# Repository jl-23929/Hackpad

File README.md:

# Hackpad

A 10-key macropad with a diagnostic LED for debugging. It's based on a Seeed XIAO RP2040.

# PCB

This is my PCB. I made it using KiCAD. It is 60x85mm and uses 2 layers with no vias.

# Enclosure

I designed the enclosure using OnShape (Fusion was completely broken at the time).

The PCB is held in with two M3 standoffs.

The bottom of the case has been countersunk for the bolt-heads.

# BOM
To build the Hackpad, the following parts are required:

11 x Cherry MX Switches
10 x Keycaps
1 x WS2812B LEDs
1 x Seeed XIAO RP2040.
1 x PCB
1 x Case (Four 3D-printed parts)
2 x 20mm M3 bolts
2 x M3 Nyloc Nuts

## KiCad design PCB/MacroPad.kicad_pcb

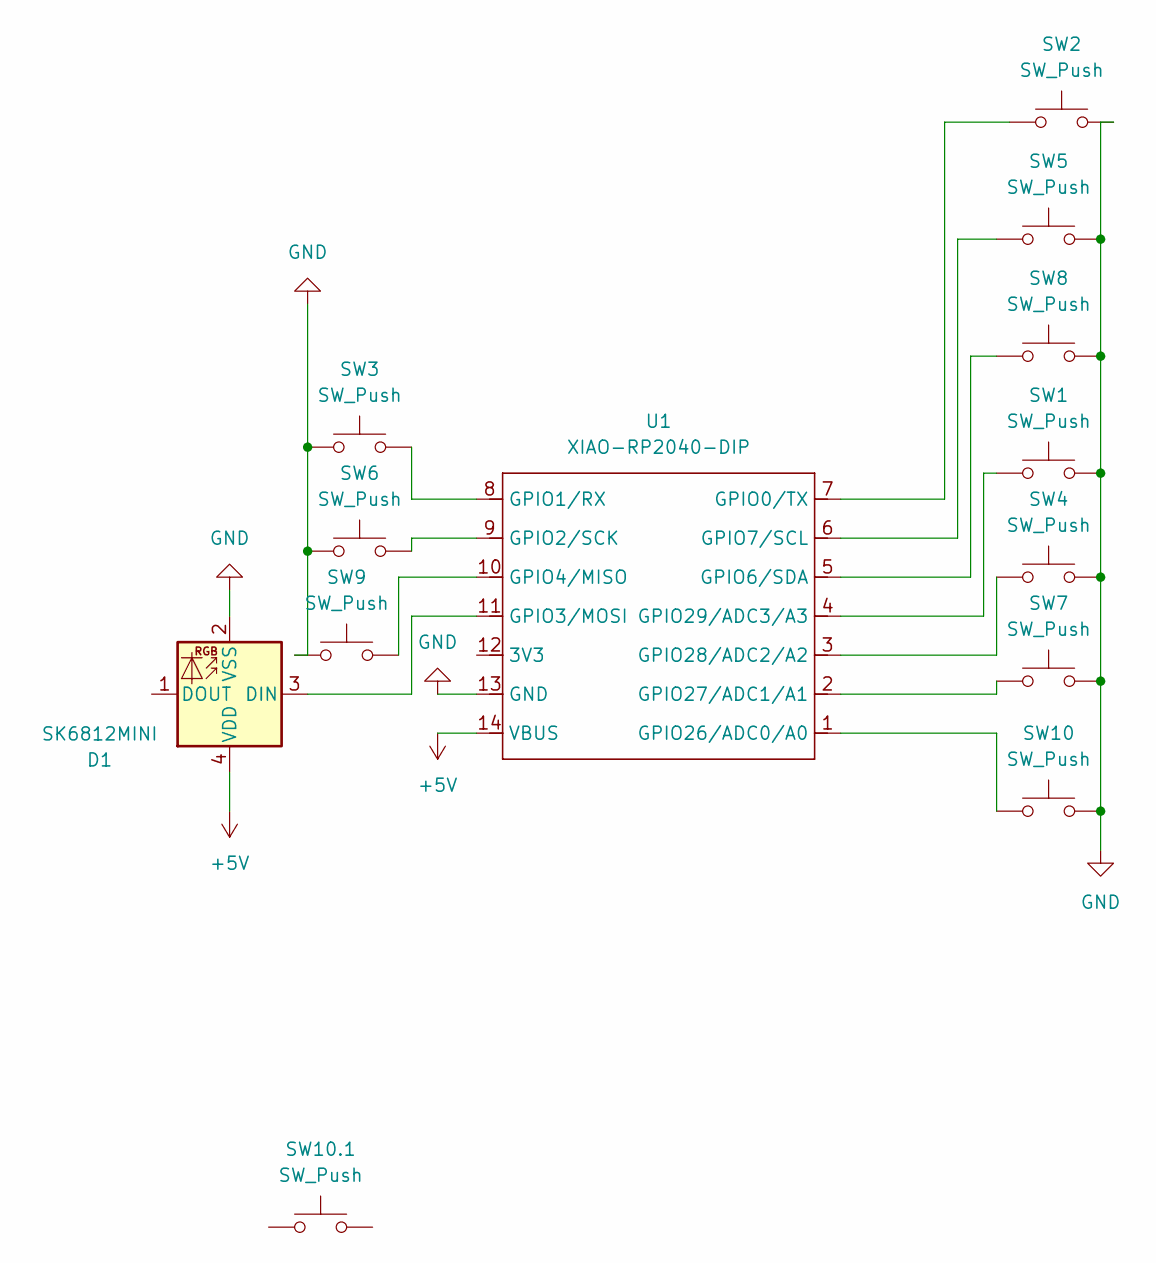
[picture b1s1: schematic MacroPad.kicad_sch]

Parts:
D1: SK6812MINI; LED_SK6812MINI_PLCC4_3.5x3.5mm_P1.75mm
SW1, SW2, SW3, SW4, SW5, SW6, SW7, SW8, SW9, SW10, SW10.1: SW_Push; SW_Cherry_MX_1.00u_PCB
U1: XIAO-RP2040-DIP

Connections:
+5V: D1.4 (VDD), U1.14 (VBUS)
GND: D1.2 (VSS), SW1.2, SW2.2, SW3.1, SW4.2, SW5.2, SW6.1, SW7.2, SW8.2, SW9.1, SW10.2, U1.13 (GND)
unnamed: D1.3 (DIN), U1.11 (GPIO3/MOSI)
unnamed: SW2.1, U1.7 (GPIO0/TX)
unnamed: SW3.2, U1.8 (GPIO1/RX)
unnamed: SW6.2, U1.9 (GPIO2/SCK)
unnamed: SW9.2, U1.10 (GPIO4/MISO)
unnamed: SW8.1, U1.5 (GPIO6/SDA)
unnamed: SW5.1, U1.6 (GPIO7/SCL)
unnamed: SW10.1, U1.1 (GPIO26/ADC0/A0)
unnamed: SW7.1, U1.2 (GPIO27/ADC1/A1)
unnamed: SW4.1, U1.3 (GPIO28/ADC2/A2)
unnamed: SW1.1, U1.4 (GPIO29/ADC3/A3)

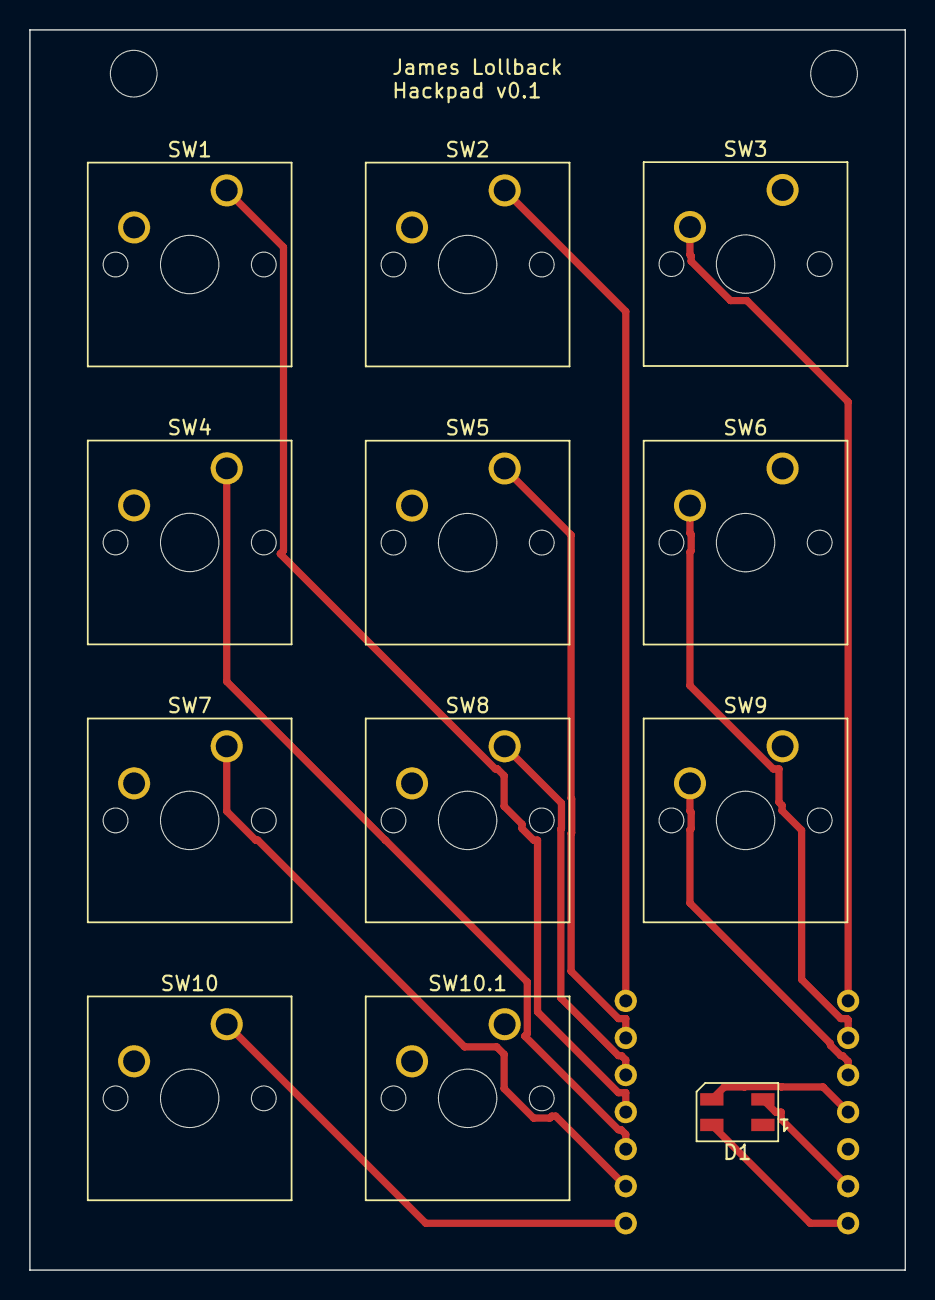
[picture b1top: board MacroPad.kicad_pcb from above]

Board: 2 copper layers, 60.0 x 85.0 mm, 13 parts (1 on the bottom side), 13 nets.

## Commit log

2025-06-30 Added firmware.
2025-07-01 Added remaining files.
